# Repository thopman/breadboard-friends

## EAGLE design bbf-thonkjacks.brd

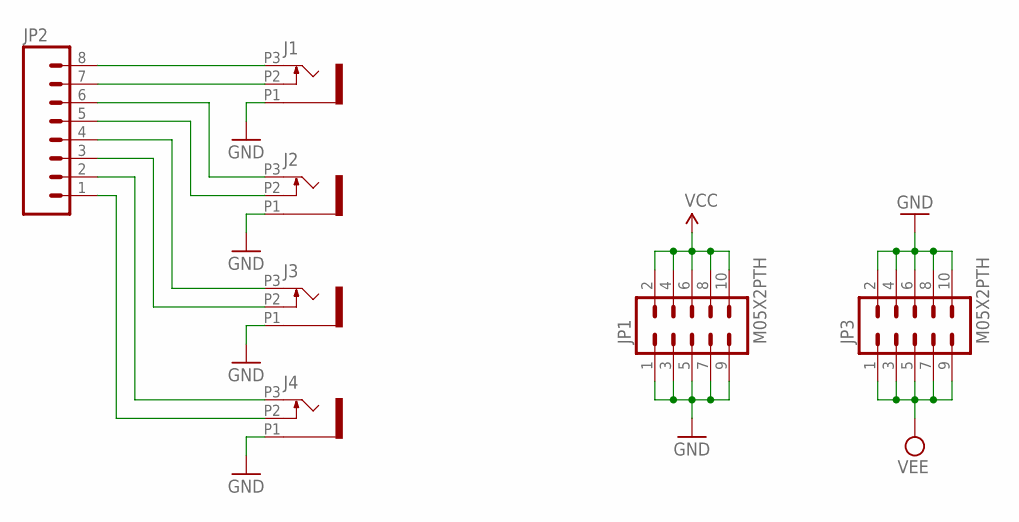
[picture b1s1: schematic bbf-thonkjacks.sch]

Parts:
J1, J2, J3, J4: OG-PJ301_PJ301_THONKICONN4; OG-PJ301_WQP_PJ_301M4
JP1, JP3: M05X2PTH; AVR_ICSP
JP2: M08; 1X08

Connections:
GND: J1.P1 (1), J2.P1 (1), J3.P1 (1), J4.P1 (1), JP1.1, JP1.3, JP1.5, JP1.7, JP1.9, JP3.2, JP3.4, JP3.6, JP3.8, JP3.10
unnamed: J2.P3 (3), JP2.6
unnamed: J2.P2 (2), JP2.5
unnamed: J3.P3 (3), JP2.4
unnamed: J3.P2 (2), JP2.3
unnamed: J4.P3 (3), JP2.2
unnamed: J4.P2 (2), JP2.1
unnamed: J1.P3 (3), JP2.8
unnamed: J1.P2 (2), JP2.7
VCC: JP1.2, JP1.4, JP1.6, JP1.8, JP1.10
VEE: JP3.1, JP3.3, JP3.5, JP3.7, JP3.9

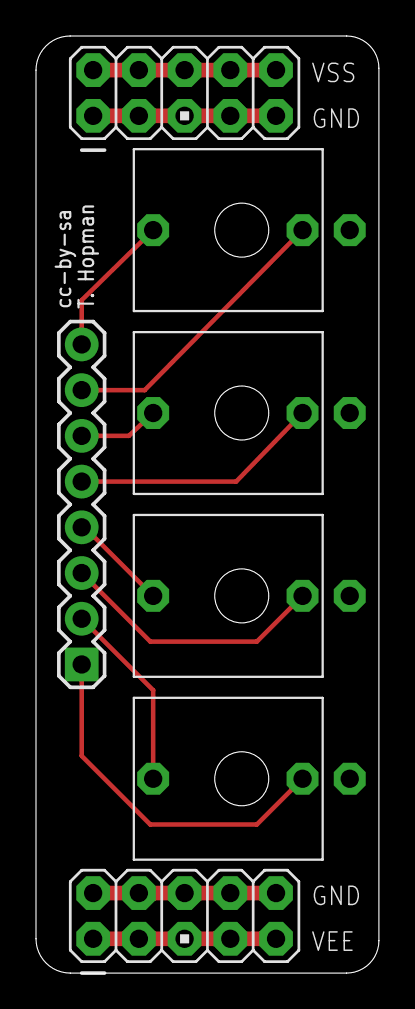
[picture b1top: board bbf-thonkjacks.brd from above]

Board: 2 copper layers, 19.1 x 52.1 mm, 7 parts (0 on the bottom side), 11 nets.

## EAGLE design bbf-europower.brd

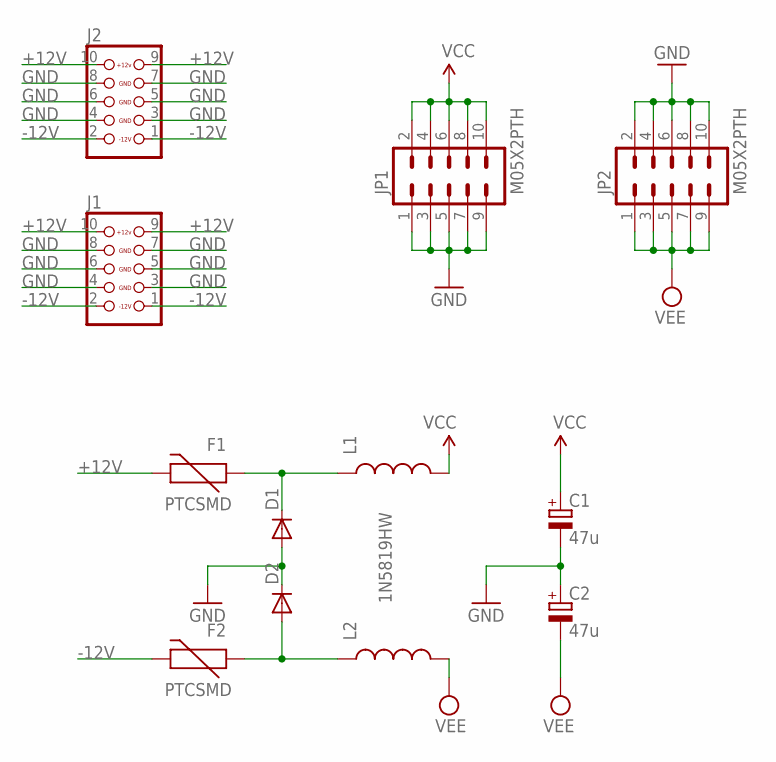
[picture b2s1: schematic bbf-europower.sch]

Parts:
C1, C2: 47u; E2-5
D1, D2: 1N5819HW; SOD123
F1, F2: PTCSMD; PTC-1206
J1, J2: CON_HEADER_2X05-PTH; M2X5
JP1, JP2: M05X2PTH; AVR_ICSP
L1, L2: INDUCTOR0603; 0603

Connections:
+12V: F1.2, J1.9, J1.10, J2.9, J2.10
-12V: F2.2, J1.1, J1.2, J2.1, J2.2
GND: C1.-, C2.+, D1.A, D2.C, J1.3, J1.4, J1.5, J1.6, J1.7, J1.8, J2.3, J2.4, J2.5, J2.6, J2.7, J2.8, JP1.1, JP1.3, JP1.5, JP1.7, JP1.9, JP2.2, JP2.4, JP2.6, JP2.8, JP2.10
unnamed: D1.C, F1.1, L1.1
unnamed: D2.A, F2.1, L2.1
VCC: C1.+, JP1.2, JP1.4, JP1.6, JP1.8, JP1.10, L1.2
VEE: C2.-, JP2.1, JP2.3, JP2.5, JP2.7, JP2.9, L2.2

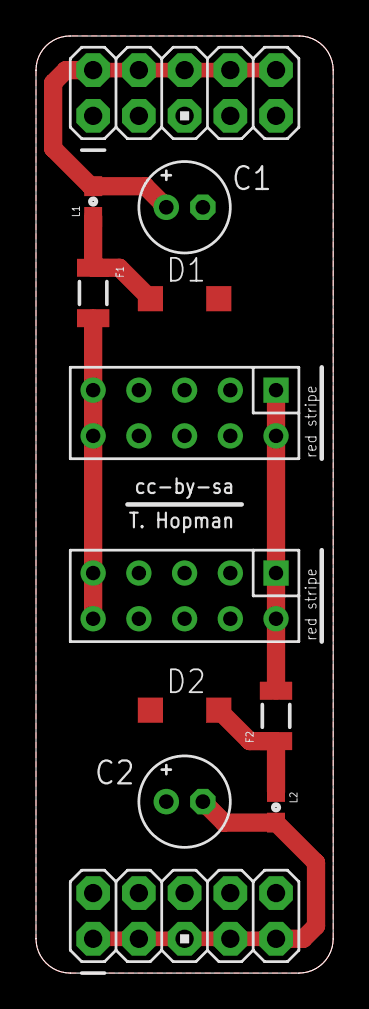
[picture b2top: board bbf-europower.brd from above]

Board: 2 copper layers, 16.5 x 52.1 mm, 12 parts (0 on the bottom side), 7 nets.

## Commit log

2016-08-19 added completely redesigned versions of gareth david johnson's (oscillosaurus) thonkjacks and europower boards.
2017-01-02 no message

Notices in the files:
bbf-europower.brd:
cc-by-sa
parts and their libraries:
SparkFun-Passives: Licensing: Creative Commons ShareAlike 4.0 International - https://creativecommons.org/licenses/by-sa/4.0
SparkFun-Aesthetics: Licensing: CC v3.0 Share-Alike You are welcome to use this library for commercial purposes.
